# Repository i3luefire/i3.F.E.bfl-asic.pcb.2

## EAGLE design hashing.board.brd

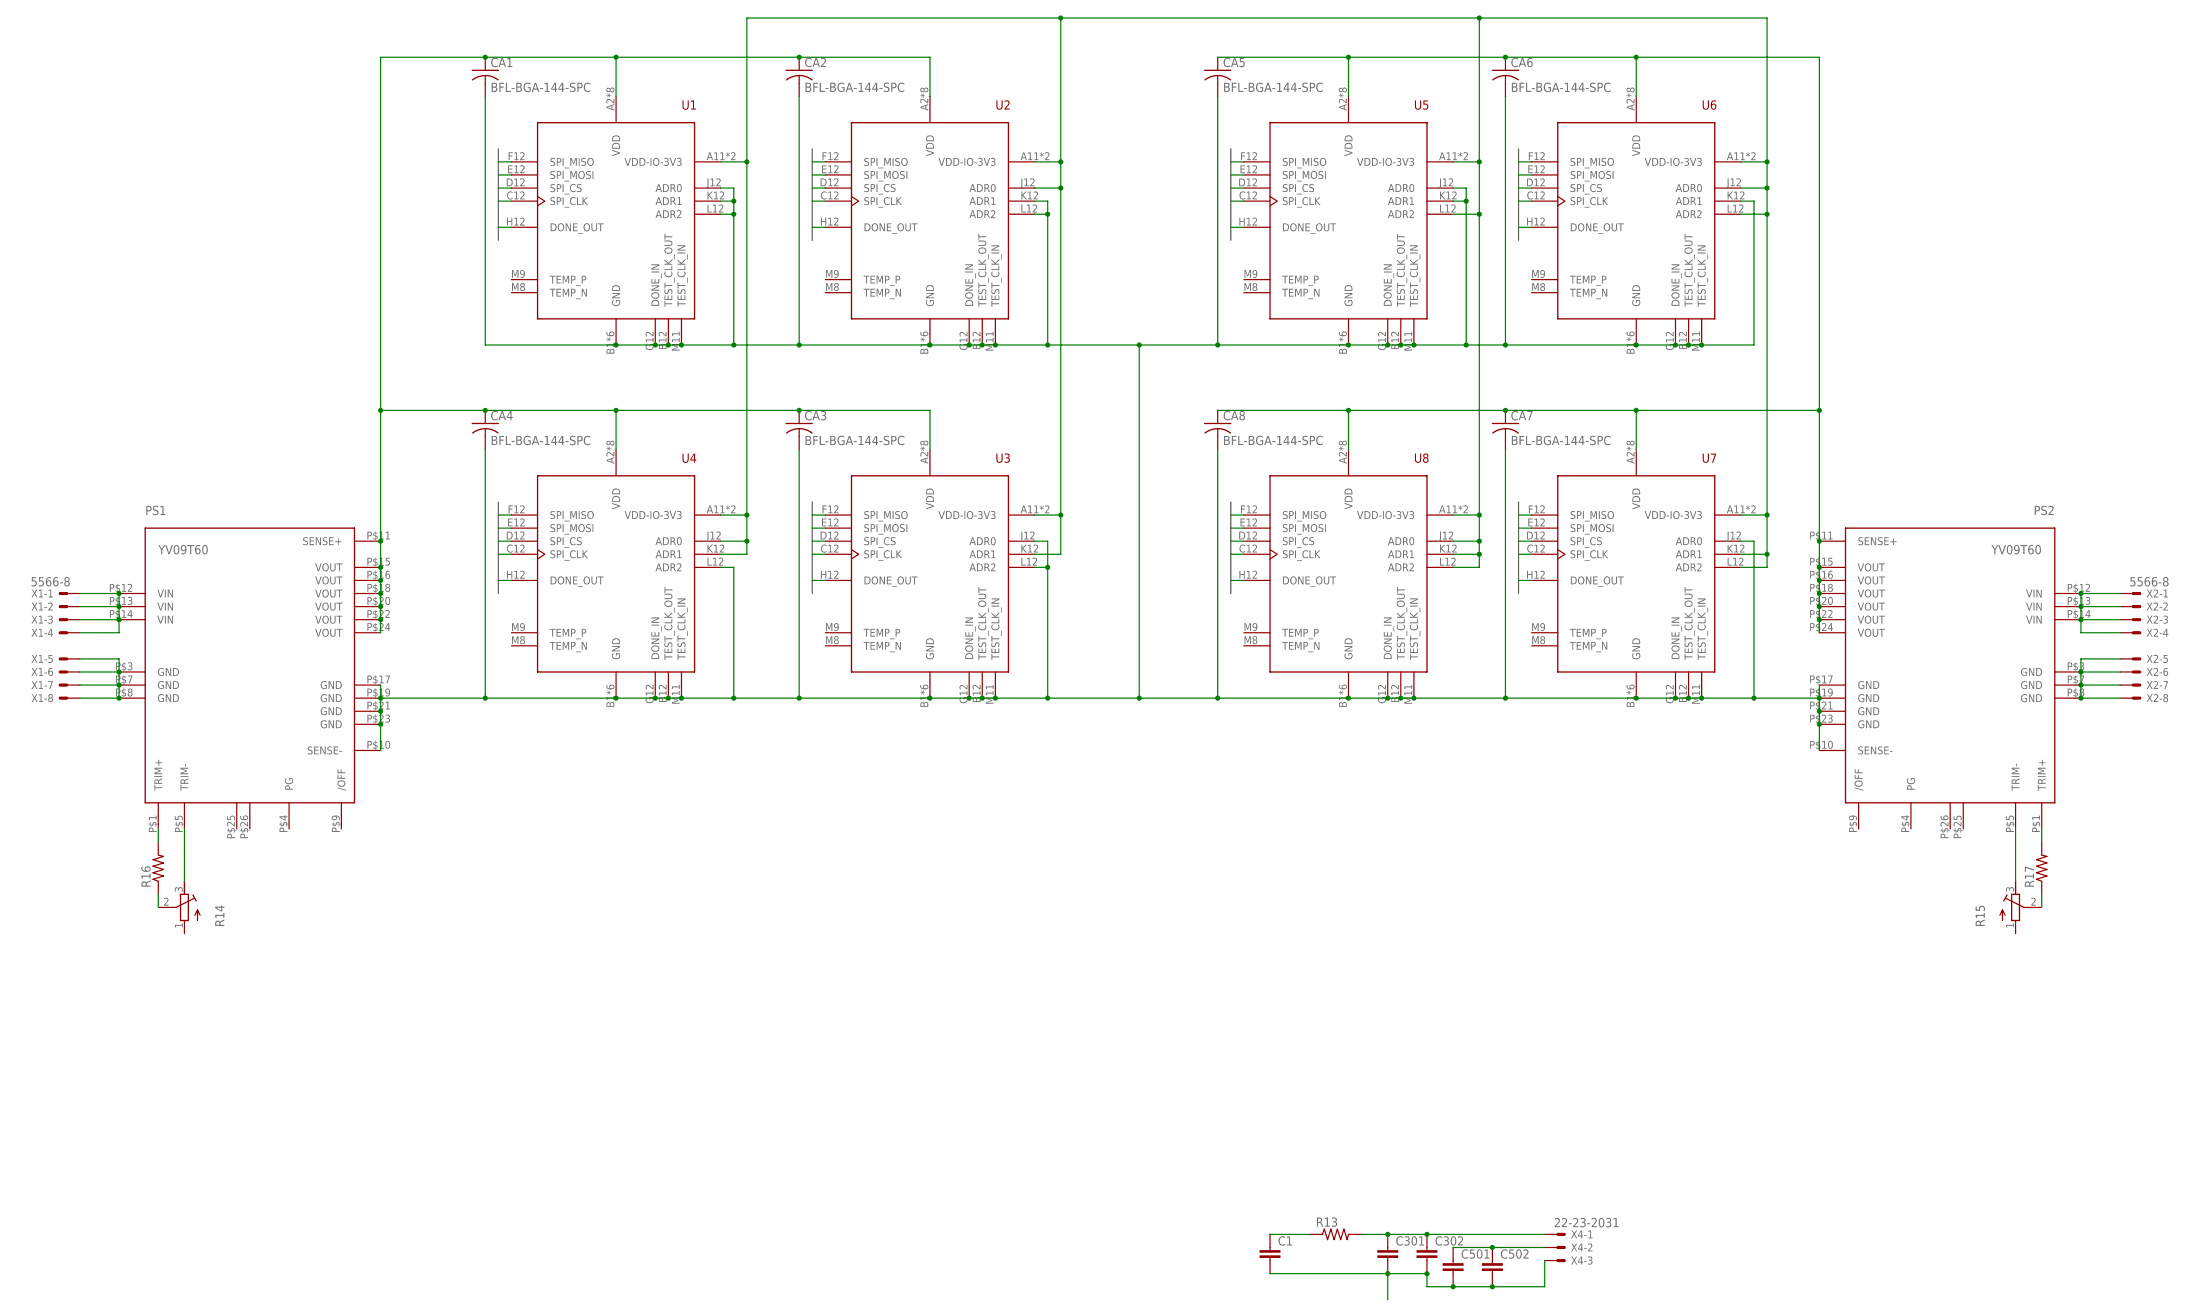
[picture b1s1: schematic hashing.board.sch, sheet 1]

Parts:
C1, C301, C501: C-EUC0805K; C0805K
C302, C502: C-EUC1210K; C1210K
CA1, CA2, CA3, CA4, CA5, CA6, CA7, CA8: BFL-BGA-144-SPC; BFL-BGA-VIA-PATTERN
PS1, PS2: YV09T60
R13, R16, R17: R-US_R0805W; R0805W
R14, R15: R-TRIMM3224J; RTRIM3224J
U1, U2, U3, U4, U5, U6, U7, U8: BFL-ASIC-1; BFL-BGA-BIG-PADS
X1, X2: 5566-8
X4: 22-23-2031

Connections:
DONE0: U1.H12 (DONE_OUT); also elsewhere on the board
DONE1: U2.H12 (DONE_OUT); also elsewhere on the board
DONE2: U3.H12 (DONE_OUT); also elsewhere on the board
DONE3: U4.H12 (DONE_OUT); also elsewhere on the board
DONE4: U5.H12 (DONE_OUT); also elsewhere on the board
DONE5: U6.H12 (DONE_OUT); also elsewhere on the board
DONE6: U8.H12 (DONE_OUT); also elsewhere on the board
DONE7: U7.H12 (DONE_OUT); also elsewhere on the board
GND: C1.2, C301.2, C302.2, C501.2, C502.2, CA1.N$2 (2), CA1.N$3 (2), CA1.N$5 (2), CA1.N$6 (2), CA1.N$8 (2), CA1.N$9 (2), CA1.N$11 (2), CA1.N$12 (2), CA1.N$14 (2), CA1.N$15 (2), CA1.N$16 (2), CA1.N$17 (2), CA1.N$19 (2), CA1.N$21 (2), CA1.N$23 (2), CA1.N$25 (2), CA1.N$27 (2), CA1.N$28 (2), CA1.N$30 (2), CA1.N$31 (2), CA1.N$33 (2), CA1.N$34 (2), CA1.N$36 (2), CA1.N$37 (2), CA1.N$39 (2), CA1.N$40 (2), CA1.N$42 (2), CA1.N$43 (2), CA1.N$44 (2), CA1.N$45 (2), CA1.N$55 (2), CA1.N$62 (2), CA1.N$64 (2), CA1.N$66 (2), CA1.N$68 (2), CA1.N$70 (2), CA1.N$72 (2), CA1.N$74 (2), CA1.N$76 (2), CA1.N$78 (2), CA1.N$80 (2), CA1.N$82 (2), CA1.N$84 (2), CA1.N$86 (2), CA1.N$88 (2), CA1.N$90 (2), CA1.N$92 (2), CA1.N$94 (2), CA1.N$98 (2), CA1.N$100 (2), CA1.N$102 (2), CA1.N$104 (2), CA1.N$106 (2), CA1.N$110 (2), CA2.N$2 (2), CA2.N$3 (2), CA2.N$5 (2), CA2.N$6 (2), CA2.N$8 (2), CA2.N$9 (2), CA2.N$11 (2), CA2.N$12 (2), CA2.N$14 (2), CA2.N$15 (2), CA2.N$16 (2), CA2.N$17 (2), CA2.N$19 (2), CA2.N$21 (2), CA2.N$23 (2), CA2.N$25 (2), CA2.N$27 (2), CA2.N$28 (2), CA2.N$30 (2), CA2.N$31 (2), CA2.N$33 (2), CA2.N$34 (2), CA2.N$36 (2), CA2.N$37 (2), CA2.N$39 (2), CA2.N$40 (2), CA2.N$42 (2), CA2.N$43 (2), CA2.N$44 (2), CA2.N$45 (2), CA2.N$55 (2), CA2.N$62 (2), CA2.N$64 (2), CA2.N$66 (2), CA2.N$68 (2), CA2.N$70 (2), CA2.N$72 (2), CA2.N$74 (2), CA2.N$76 (2), CA2.N$78 (2), CA2.N$80 (2), CA2.N$82 (2), CA2.N$84 (2), CA2.N$86 (2), CA2.N$88 (2), CA2.N$90 (2), CA2.N$92 (2), CA2.N$94 (2), CA2.N$98 (2), CA2.N$100 (2), CA2.N$102 (2), CA2.N$104 (2), CA2.N$106 (2), CA2.N$110 (2), CA3.N$2 (2), CA3.N$3 (2), CA3.N$5 (2), CA3.N$6 (2), CA3.N$8 (2), CA3.N$9 (2), CA3.N$11 (2), CA3.N$12 (2), CA3.N$14 (2), CA3.N$15 (2), CA3.N$16 (2), CA3.N$17 (2), CA3.N$19 (2), CA3.N$21 (2), CA3.N$23 (2), CA3.N$25 (2), CA3.N$27 (2), CA3.N$28 (2), CA3.N$30 (2), CA3.N$31 (2), CA3.N$33 (2), CA3.N$34 (2), CA3.N$36 (2), CA3.N$37 (2), CA3.N$39 (2), CA3.N$40 (2), CA3.N$42 (2), CA3.N$43 (2), CA3.N$44 (2), CA3.N$45 (2), CA3.N$55 (2), CA3.N$62 (2), CA3.N$64 (2), CA3.N$66 (2), CA3.N$68 (2), CA3.N$70 (2), CA3.N$72 (2), CA3.N$74 (2), CA3.N$76 (2), CA3.N$78 (2), CA3.N$80 (2), CA3.N$82 (2), CA3.N$84 (2), CA3.N$86 (2), CA3.N$88 (2), CA3.N$90 (2), CA3.N$92 (2), CA3.N$94 (2), CA3.N$98 (2), CA3.N$100 (2), CA3.N$102 (2), CA3.N$104 (2), CA3.N$106 (2), CA3.N$110 (2), CA4.N$2 (2), CA4.N$3 (2), CA4.N$5 (2), CA4.N$6 (2), CA4.N$8 (2), CA4.N$9 (2), CA4.N$11 (2), CA4.N$12 (2), CA4.N$14 (2), CA4.N$15 (2), CA4.N$16 (2), CA4.N$17 (2), CA4.N$19 (2), CA4.N$21 (2), CA4.N$23 (2), CA4.N$25 (2), CA4.N$27 (2), CA4.N$28 (2), CA4.N$30 (2), CA4.N$31 (2), CA4.N$33 (2), CA4.N$34 (2), CA4.N$36 (2), CA4.N$37 (2), CA4.N$39 (2), CA4.N$40 (2), CA4.N$42 (2), CA4.N$43 (2), CA4.N$44 (2), CA4.N$45 (2), CA4.N$55 (2), CA4.N$62 (2), CA4.N$64 (2), CA4.N$66 (2), CA4.N$68 (2), CA4.N$70 (2), CA4.N$72 (2), CA4.N$74 (2), CA4.N$76 (2), CA4.N$78 (2), CA4.N$80 (2), CA4.N$82 (2), CA4.N$84 (2), CA4.N$86 (2), CA4.N$88 (2), CA4.N$90 (2), CA4.N$92 (2), CA4.N$94 (2), CA4.N$98 (2), CA4.N$100 (2), CA4.N$102 (2), CA4.N$104 (2), CA4.N$106 (2), CA4.N$110 (2), CA5.N$2 (2), CA5.N$3 (2), CA5.N$5 (2), CA5.N$6 (2), CA5.N$8 (2), CA5.N$9 (2), CA5.N$11 (2), CA5.N$12 (2), CA5.N$14 (2), CA5.N$15 (2), CA5.N$16 (2), CA5.N$17 (2), CA5.N$19 (2), CA5.N$21 (2), CA5.N$23 (2), CA5.N$25 (2), CA5.N$27 (2), CA5.N$28 (2), CA5.N$30 (2), CA5.N$31 (2), CA5.N$33 (2), CA5.N$34 (2), CA5.N$36 (2), CA5.N$37 (2), CA5.N$39 (2), CA5.N$40 (2), CA5.N$42 (2), CA5.N$43 (2), CA5.N$44 (2), CA5.N$45 (2), CA5.N$55 (2), CA5.N$62 (2), CA5.N$64 (2), CA5.N$66 (2), CA5.N$68 (2), CA5.N$70 (2), CA5.N$72 (2), CA5.N$74 (2), CA5.N$76 (2), CA5.N$78 (2), CA5.N$80 (2), CA5.N$82 (2), CA5.N$84 (2), CA5.N$86 (2), CA5.N$88 (2), CA5.N$90 (2), CA5.N$92 (2), CA5.N$94 (2), CA5.N$98 (2), CA5.N$100 (2), CA5.N$102 (2), CA5.N$104 (2), CA5.N$106 (2), CA5.N$110 (2), CA6.N$2 (2), CA6.N$3 (2), CA6.N$5 (2), CA6.N$6 (2), CA6.N$8 (2), CA6.N$9 (2), CA6.N$11 (2), CA6.N$12 (2), CA6.N$14 (2), CA6.N$15 (2), CA6.N$16 (2), CA6.N$17 (2), CA6.N$19 (2), CA6.N$21 (2), CA6.N$23 (2), CA6.N$25 (2), CA6.N$27 (2), CA6.N$28 (2), CA6.N$30 (2), CA6.N$31 (2), CA6.N$33 (2), CA6.N$34 (2), CA6.N$36 (2), CA6.N$37 (2), CA6.N$39 (2), CA6.N$40 (2), CA6.N$42 (2), CA6.N$43 (2), CA6.N$44 (2), CA6.N$45 (2), CA6.N$55 (2), CA6.N$62 (2), CA6.N$64 (2), CA6.N$66 (2), CA6.N$68 (2), CA6.N$70 (2), CA6.N$72 (2), CA6.N$74 (2), CA6.N$76 (2), CA6.N$78 (2), CA6.N$80 (2), CA6.N$82 (2), CA6.N$84 (2), CA6.N$86 (2), CA6.N$88 (2), CA6.N$90 (2), CA6.N$92 (2), CA6.N$94 (2), CA6.N$98 (2), CA6.N$100 (2), CA6.N$102 (2), CA6.N$104 (2), CA6.N$106 (2), CA6.N$110 (2), CA7.N$2 (2), CA7.N$3 (2), CA7.N$5 (2), CA7.N$6 (2), CA7.N$8 (2), CA7.N$9 (2), CA7.N$11 (2), CA7.N$12 (2), CA7.N$14 (2), CA7.N$15 (2), CA7.N$16 (2), CA7.N$17 (2), CA7.N$19 (2), CA7.N$21 (2), CA7.N$23 (2), CA7.N$25 (2), CA7.N$27 (2), CA7.N$28 (2), CA7.N$30 (2), CA7.N$31 (2), CA7.N$33 (2), CA7.N$34 (2), CA7.N$36 (2), CA7.N$37 (2), CA7.N$39 (2), CA7.N$40 (2), CA7.N$42 (2), CA7.N$43 (2), CA7.N$44 (2), CA7.N$45 (2), CA7.N$55 (2), CA7.N$62 (2), CA7.N$64 (2), CA7.N$66 (2), CA7.N$68 (2), CA7.N$70 (2), CA7.N$72 (2), CA7.N$74 (2), CA7.N$76 (2), CA7.N$78 (2), CA7.N$80 (2), CA7.N$82 (2), CA7.N$84 (2), CA7.N$86 (2), CA7.N$88 (2), CA7.N$90 (2), CA7.N$92 (2), CA7.N$94 (2), CA7.N$98 (2), CA7.N$100 (2), CA7.N$102 (2), CA7.N$104 (2), CA7.N$106 (2), CA7.N$110 (2), CA8.N$2 (2), CA8.N$3 (2), CA8.N$5 (2), CA8.N$6 (2), CA8.N$8 (2), CA8.N$9 (2), CA8.N$11 (2), CA8.N$12 (2), CA8.N$14 (2), CA8.N$15 (2), CA8.N$16 (2), CA8.N$17 (2), CA8.N$19 (2), CA8.N$21 (2), CA8.N$23 (2), CA8.N$25 (2), CA8.N$27 (2), CA8.N$28 (2), CA8.N$30 (2), CA8.N$31 (2), CA8.N$33 (2), CA8.N$34 (2), CA8.N$36 (2), CA8.N$37 (2), CA8.N$39 (2), CA8.N$40 (2), CA8.N$42 (2), CA8.N$43 (2), CA8.N$44 (2), CA8.N$45 (2), CA8.N$55 (2), CA8.N$62 (2), CA8.N$64 (2), CA8.N$66 (2), CA8.N$68 (2), CA8.N$70 (2), CA8.N$72 (2), CA8.N$74 (2), CA8.N$76 (2), CA8.N$78 (2), CA8.N$80 (2), CA8.N$82 (2), CA8.N$84 (2), CA8.N$86 (2), CA8.N$88 (2), CA8.N$90 (2), CA8.N$92 (2), CA8.N$94 (2), CA8.N$98 (2), CA8.N$100 (2), CA8.N$102 (2), CA8.N$104 (2), CA8.N$106 (2), CA8.N$110 (2), PS1.P$3 (GND), PS1.P$7 (GND), PS1.P$8 (GND), PS1.P$10 (SENSE-), PS1.P$17 (GND), PS1.P$19 (GND), PS1.P$21 (GND), PS1.P$23 (GND), PS2.P$3 (GND), PS2.P$7 (GND), PS2.P$8 (GND), PS2.P$10 (SENSE-), PS2.P$17 (GND), PS2.P$19 (GND), PS2.P$21 (GND), PS2.P$23 (GND), U1.B1 (GND), U1.B3 (GND), U1.B5 (GND), U1.B7 (GND), U1.B9 (GND), U1.B11 (GND), U1.B12 (TEST_CLK_OUT), U1.G12 (DONE_IN), U1.J12 (ADR0), U1.K12 (ADR1), U1.L12 (ADR2), U1.M11 (TEST_CLK_IN), U2.B1 (GND), U2.B3 (GND), U2.B5 (GND), U2.B7 (GND), U2.B9 (GND), U2.B11 (GND), U2.B12 (TEST_CLK_OUT), U2.G12 (DONE_IN), U2.K12 (ADR1), U2.L12 (ADR2), U2.M11 (TEST_CLK_IN), U3.B1 (GND), U3.B3 (GND), U3.B5 (GND), U3.B7 (GND), U3.B9 (GND), U3.B11 (GND), U3.B12 (TEST_CLK_OUT), U3.G12 (DONE_IN), U3.J12 (ADR0), U3.L12 (ADR2), U3.M11 (TEST_CLK_IN), U4.B1 (GND), U4.B3 (GND), U4.B5 (GND), U4.B7 (GND), U4.B9 (GND), U4.B11 (GND), U4.B12 (TEST_CLK_OUT), U4.G12 (DONE_IN), U4.L12 (ADR2), U4.M11 (TEST_CLK_IN), U5.B1 (GND), U5.B3 (GND), U5.B5 (GND), U5.B7 (GND), U5.B9 (GND), U5.B11 (GND), U5.B12 (TEST_CLK_OUT), U5.G12 (DONE_IN), U5.J12 (ADR0), U5.K12 (ADR1), U5.M11 (TEST_CLK_IN), U6.B1 (GND), U6.B3 (GND), U6.B5 (GND), U6.B7 (GND), U6.B9 (GND), U6.B11 (GND), U6.B12 (TEST_CLK_OUT), U6.G12 (DONE_IN), U6.K12 (ADR1), U6.M11 (TEST_CLK_IN), U7.B1 (GND), U7.B3 (GND), U7.B5 (GND), U7.B7 (GND), U7.B9 (GND), U7.B11 (GND), U7.B12 (TEST_CLK_OUT), U7.G12 (DONE_IN), U7.J12 (ADR0), U7.M11 (TEST_CLK_IN), U8.B1 (GND), U8.B3 (GND), U8.B5 (GND), U8.B7 (GND), U8.B9 (GND), U8.B11 (GND), U8.B12 (TEST_CLK_OUT), U8.G12 (DONE_IN), U8.M11 (TEST_CLK_IN), X1.5, X1.6, X1.7, X1.8, X2.5, X2.6, X2.7, X2.8, X4.3; also elsewhere on the board
unnamed: R15.2 (S), R17.1
unnamed: PS2.P$1 (TRIM+), R17.2
unnamed: PS2.P$5 (TRIM-), R15.3 (A)
unnamed: PS1.P$5 (TRIM-), R14.3 (A)
unnamed: R14.2 (S), R16.1
unnamed: PS1.P$1 (TRIM+), R16.2
SPI_1_CLK: U1.C12 (SPI_CLK), U2.C12 (SPI_CLK), U3.C12 (SPI_CLK), U4.C12 (SPI_CLK), U5.C12 (SPI_CLK), U6.C12 (SPI_CLK), U7.C12 (SPI_CLK), U8.C12 (SPI_CLK); also elsewhere on the board
SPI_1_CS: U1.D12 (SPI_CS), U2.D12 (SPI_CS), U3.D12 (SPI_CS), U4.D12 (SPI_CS), U5.D12 (SPI_CS), U6.D12 (SPI_CS), U7.D12 (SPI_CS), U8.D12 (SPI_CS); also elsewhere on the board
SPI_1_MISO: U1.F12 (SPI_MISO), U2.F12 (SPI_MISO), U3.F12 (SPI_MISO), U4.F12 (SPI_MISO), U5.F12 (SPI_MISO), U6.F12 (SPI_MISO), U7.F12 (SPI_MISO), U8.F12 (SPI_MISO); also elsewhere on the board
SPI_1_MOSI: U1.E12 (SPI_MOSI), U2.E12 (SPI_MOSI), U3.E12 (SPI_MOSI), U4.E12 (SPI_MOSI), U5.E12 (SPI_MOSI), U6.E12 (SPI_MOSI), U7.E12 (SPI_MOSI), U8.E12 (SPI_MOSI); also elsewhere on the board
VDD-1A: CA1.P$1 (1), CA1.P$4 (1), CA1.P$7 (1), CA1.P$10 (1), CA1.P$13 (1), CA1.P$18 (1), CA1.P$20 (1), CA1.P$22 (1), CA1.P$24 (1), CA1.P$26 (1), CA1.P$29 (1), CA1.P$32 (1), CA1.P$35 (1), CA1.P$38 (1), CA1.P$41 (1), CA1.P$46 (1), CA1.P$47 (1), CA1.P$48 (1), CA1.P$50 (1), CA1.P$51 (1), CA1.P$52 (1), CA1.P$53 (1), CA1.P$54 (1), CA1.P$56 (1), CA1.P$57 (1), CA1.P$58 (1), CA1.P$59 (1), CA1.P$60 (1), CA1.P$61 (1), CA1.P$63 (1), CA1.P$65 (1), CA1.P$67 (1), CA1.P$69 (1), CA1.P$71 (1), CA1.P$73 (1), CA1.P$75 (1), CA1.P$77 (1), CA1.P$79 (1), CA1.P$81 (1), CA1.P$83 (1), CA1.P$85 (1), CA1.P$87 (1), CA1.P$89 (1), CA1.P$91 (1), CA1.P$93 (1), CA1.P$95 (1), CA1.P$99 (1), CA1.P$101 (1), CA1.P$103 (1), CA1.P$105 (1), CA1.P$107 (1), CA1.P$111 (1), CA2.P$1 (1), CA2.P$4 (1), CA2.P$7 (1), CA2.P$10 (1), CA2.P$13 (1), CA2.P$18 (1), CA2.P$20 (1), CA2.P$22 (1), CA2.P$24 (1), CA2.P$26 (1), CA2.P$29 (1), CA2.P$32 (1), CA2.P$35 (1), CA2.P$38 (1), CA2.P$41 (1), CA2.P$46 (1), CA2.P$47 (1), CA2.P$48 (1), CA2.P$50 (1), CA2.P$51 (1), CA2.P$52 (1), CA2.P$53 (1), CA2.P$54 (1), CA2.P$56 (1), CA2.P$57 (1), CA2.P$58 (1), CA2.P$59 (1), CA2.P$60 (1), CA2.P$61 (1), CA2.P$63 (1), CA2.P$65 (1), CA2.P$67 (1), CA2.P$69 (1), CA2.P$71 (1), CA2.P$73 (1), CA2.P$75 (1), CA2.P$77 (1), CA2.P$79 (1), CA2.P$81 (1), CA2.P$83 (1), CA2.P$85 (1), CA2.P$87 (1), CA2.P$89 (1), CA2.P$91 (1), CA2.P$93 (1), CA2.P$95 (1), CA2.P$99 (1), CA2.P$101 (1), CA2.P$103 (1), CA2.P$105 (1), CA2.P$107 (1), CA2.P$111 (1), CA3.P$1 (1), CA3.P$4 (1), CA3.P$7 (1), CA3.P$10 (1), CA3.P$13 (1), CA3.P$18 (1), CA3.P$20 (1), CA3.P$22 (1), CA3.P$24 (1), CA3.P$26 (1), CA3.P$29 (1), CA3.P$32 (1), CA3.P$35 (1), CA3.P$38 (1), CA3.P$41 (1), CA3.P$46 (1), CA3.P$47 (1), CA3.P$48 (1), CA3.P$50 (1), CA3.P$51 (1), CA3.P$52 (1), CA3.P$53 (1), CA3.P$54 (1), CA3.P$56 (1), CA3.P$57 (1), CA3.P$58 (1), CA3.P$59 (1), CA3.P$60 (1), CA3.P$61 (1), CA3.P$63 (1), CA3.P$65 (1), CA3.P$67 (1), CA3.P$69 (1), CA3.P$71 (1), CA3.P$73 (1), CA3.P$75 (1), CA3.P$77 (1), CA3.P$79 (1), CA3.P$81 (1), CA3.P$83 (1), CA3.P$85 (1), CA3.P$87 (1), CA3.P$89 (1), CA3.P$91 (1), CA3.P$93 (1), CA3.P$95 (1), CA3.P$99 (1), CA3.P$101 (1), CA3.P$103 (1), CA3.P$105 (1), CA3.P$107 (1), CA3.P$111 (1), CA4.P$1 (1), CA4.P$4 (1), CA4.P$7 (1), CA4.P$10 (1), CA4.P$13 (1), CA4.P$18 (1), CA4.P$20 (1), CA4.P$22 (1), CA4.P$24 (1), CA4.P$26 (1), CA4.P$29 (1), CA4.P$32 (1), CA4.P$35 (1), CA4.P$38 (1), CA4.P$41 (1), CA4.P$46 (1), CA4.P$47 (1), CA4.P$48 (1), CA4.P$50 (1), CA4.P$51 (1), CA4.P$52 (1), CA4.P$53 (1), CA4.P$54 (1), CA4.P$56 (1), CA4.P$57 (1), CA4.P$58 (1), CA4.P$59 (1), CA4.P$60 (1), CA4.P$61 (1), CA4.P$63 (1), CA4.P$65 (1), CA4.P$67 (1), CA4.P$69 (1), CA4.P$71 (1), CA4.P$73 (1), CA4.P$75 (1), CA4.P$77 (1), CA4.P$79 (1), CA4.P$81 (1), CA4.P$83 (1), CA4.P$85 (1), CA4.P$87 (1), CA4.P$89 (1), CA4.P$91 (1), CA4.P$93 (1), CA4.P$95 (1), CA4.P$99 (1), CA4.P$101 (1), CA4.P$103 (1), CA4.P$105 (1), CA4.P$107 (1), CA4.P$111 (1), PS1.P$11 (SENSE+), PS1.P$15 (VOUT), PS1.P$16 (VOUT), PS1.P$18 (VOUT), PS1.P$20 (VOUT), PS1.P$22 (VOUT), PS1.P$24 (VOUT), U1.A2 (VDD), U1.A4 (VDD), U1.A6 (VDD), U1.A8 (VDD), U1.A9 (VDD), U1.A10 (VDD), U1.M5 (VDD), U1.M7 (VDD), U2.A2 (VDD), U2.A4 (VDD), U2.A6 (VDD), U2.A8 (VDD), U2.A9 (VDD), U2.A10 (VDD), U2.M5 (VDD), U2.M7 (VDD), U3.A2 (VDD), U3.A4 (VDD), U3.A6 (VDD), U3.A8 (VDD), U3.A9 (VDD), U3.A10 (VDD), U3.M5 (VDD), U3.M7 (VDD), U4.A2 (VDD), U4.A4 (VDD), U4.A6 (VDD), U4.A8 (VDD), U4.A9 (VDD), U4.A10 (VDD), U4.M5 (VDD), U4.M7 (VDD)
VDD-1B: CA5.P$1 (1), CA5.P$4 (1), CA5.P$7 (1), CA5.P$10 (1), CA5.P$13 (1), CA5.P$18 (1), CA5.P$20 (1), CA5.P$22 (1), CA5.P$24 (1), CA5.P$26 (1), CA5.P$29 (1), CA5.P$32 (1), CA5.P$35 (1), CA5.P$38 (1), CA5.P$41 (1), CA5.P$46 (1), CA5.P$47 (1), CA5.P$48 (1), CA5.P$50 (1), CA5.P$51 (1), CA5.P$52 (1), CA5.P$53 (1), CA5.P$54 (1), CA5.P$56 (1), CA5.P$57 (1), CA5.P$58 (1), CA5.P$59 (1), CA5.P$60 (1), CA5.P$61 (1), CA5.P$63 (1), CA5.P$65 (1), CA5.P$67 (1), CA5.P$69 (1), CA5.P$71 (1), CA5.P$73 (1), CA5.P$75 (1), CA5.P$77 (1), CA5.P$79 (1), CA5.P$81 (1), CA5.P$83 (1), CA5.P$85 (1), CA5.P$87 (1), CA5.P$89 (1), CA5.P$91 (1), CA5.P$93 (1), CA5.P$95 (1), CA5.P$99 (1), CA5.P$101 (1), CA5.P$103 (1), CA5.P$105 (1), CA5.P$107 (1), CA5.P$111 (1), CA6.P$1 (1), CA6.P$4 (1), CA6.P$7 (1), CA6.P$10 (1), CA6.P$13 (1), CA6.P$18 (1), CA6.P$20 (1), CA6.P$22 (1), CA6.P$24 (1), CA6.P$26 (1), CA6.P$29 (1), CA6.P$32 (1), CA6.P$35 (1), CA6.P$38 (1), CA6.P$41 (1), CA6.P$46 (1), CA6.P$47 (1), CA6.P$48 (1), CA6.P$50 (1), CA6.P$51 (1), CA6.P$52 (1), CA6.P$53 (1), CA6.P$54 (1), CA6.P$56 (1), CA6.P$57 (1), CA6.P$58 (1), CA6.P$59 (1), CA6.P$60 (1), CA6.P$61 (1), CA6.P$63 (1), CA6.P$65 (1), CA6.P$67 (1), CA6.P$69 (1), CA6.P$71 (1), CA6.P$73 (1), CA6.P$75 (1), CA6.P$77 (1), CA6.P$79 (1), CA6.P$81 (1), CA6.P$83 (1), CA6.P$85 (1), CA6.P$87 (1), CA6.P$89 (1), CA6.P$91 (1), CA6.P$93 (1), CA6.P$95 (1), CA6.P$99 (1), CA6.P$101 (1), CA6.P$103 (1), CA6.P$105 (1), CA6.P$107 (1), CA6.P$111 (1), CA7.P$1 (1), CA7.P$4 (1), CA7.P$7 (1), CA7.P$10 (1), CA7.P$13 (1), CA7.P$18 (1), CA7.P$20 (1), CA7.P$22 (1), CA7.P$24 (1), CA7.P$26 (1), CA7.P$29 (1), CA7.P$32 (1), CA7.P$35 (1), CA7.P$38 (1), CA7.P$41 (1), CA7.P$46 (1), CA7.P$47 (1), CA7.P$48 (1), CA7.P$50 (1), CA7.P$51 (1), CA7.P$52 (1), CA7.P$53 (1), CA7.P$54 (1), CA7.P$56 (1), CA7.P$57 (1), CA7.P$58 (1), CA7.P$59 (1), CA7.P$60 (1), CA7.P$61 (1), CA7.P$63 (1), CA7.P$65 (1), CA7.P$67 (1), CA7.P$69 (1), CA7.P$71 (1), CA7.P$73 (1), CA7.P$75 (1), CA7.P$77 (1), CA7.P$79 (1), CA7.P$81 (1), CA7.P$83 (1), CA7.P$85 (1), CA7.P$87 (1), CA7.P$89 (1), CA7.P$91 (1), CA7.P$93 (1), CA7.P$95 (1), CA7.P$99 (1), CA7.P$101 (1), CA7.P$103 (1), CA7.P$105 (1), CA7.P$107 (1), CA7.P$111 (1), CA8.P$1 (1), CA8.P$4 (1), CA8.P$7 (1), CA8.P$10 (1), CA8.P$13 (1), CA8.P$18 (1), CA8.P$20 (1), CA8.P$22 (1), CA8.P$24 (1), CA8.P$26 (1), CA8.P$29 (1), CA8.P$32 (1), CA8.P$35 (1), CA8.P$38 (1), CA8.P$41 (1), CA8.P$46 (1), CA8.P$47 (1), CA8.P$48 (1), CA8.P$50 (1), CA8.P$51 (1), CA8.P$52 (1), CA8.P$53 (1), CA8.P$54 (1), CA8.P$56 (1), CA8.P$57 (1), CA8.P$58 (1), CA8.P$59 (1), CA8.P$60 (1), CA8.P$61 (1), CA8.P$63 (1), CA8.P$65 (1), CA8.P$67 (1), CA8.P$69 (1), CA8.P$71 (1), CA8.P$73 (1), CA8.P$75 (1), CA8.P$77 (1), CA8.P$79 (1), CA8.P$81 (1), CA8.P$83 (1), CA8.P$85 (1), CA8.P$87 (1), CA8.P$89 (1), CA8.P$91 (1), CA8.P$93 (1), CA8.P$95 (1), CA8.P$99 (1), CA8.P$101 (1), CA8.P$103 (1), CA8.P$105 (1), CA8.P$107 (1), CA8.P$111 (1), PS2.P$11 (SENSE+), PS2.P$15 (VOUT), PS2.P$16 (VOUT), PS2.P$18 (VOUT), PS2.P$20 (VOUT), PS2.P$22 (VOUT), PS2.P$24 (VOUT), U5.A2 (VDD), U5.A4 (VDD), U5.A6 (VDD), U5.A8 (VDD), U5.A9 (VDD), U5.A10 (VDD), U5.M5 (VDD), U5.M7 (VDD), U6.A2 (VDD), U6.A4 (VDD), U6.A6 (VDD), U6.A8 (VDD), U6.A9 (VDD), U6.A10 (VDD), U6.M5 (VDD), U6.M7 (VDD), U7.A2 (VDD), U7.A4 (VDD), U7.A6 (VDD), U7.A8 (VDD), U7.A9 (VDD), U7.A10 (VDD), U7.M5 (VDD), U7.M7 (VDD), U8.A2 (VDD), U8.A4 (VDD), U8.A6 (VDD), U8.A8 (VDD), U8.A9 (VDD), U8.A10 (VDD), U8.M5 (VDD), U8.M7 (VDD)
VDD-3V3: C1.1, R13.1, U1.A11 (VDD-IO-3V3), U1.M10 (VDD-IO-3V3), U2.A11 (VDD-IO-3V3), U2.J12 (ADR0), U2.M10 (VDD-IO-3V3), U3.A11 (VDD-IO-3V3), U3.K12 (ADR1), U3.M10 (VDD-IO-3V3), U4.A11 (VDD-IO-3V3), U4.J12 (ADR0), U4.K12 (ADR1), U4.M10 (VDD-IO-3V3), U5.A11 (VDD-IO-3V3), U5.L12 (ADR2), U5.M10 (VDD-IO-3V3), U6.A11 (VDD-IO-3V3), U6.J12 (ADR0), U6.L12 (ADR2), U6.M10 (VDD-IO-3V3), U7.A11 (VDD-IO-3V3), U7.K12 (ADR1), U7.L12 (ADR2), U7.M10 (VDD-IO-3V3), U8.A11 (VDD-IO-3V3), U8.J12 (ADR0), U8.K12 (ADR1), U8.L12 (ADR2), U8.M10 (VDD-IO-3V3)
VIN1: PS1.P$12 (VIN), PS1.P$13 (VIN), PS1.P$14 (VIN), X1.1, X1.2, X1.3, X1.4
VIN2: PS2.P$12 (VIN), PS2.P$13 (VIN), PS2.P$14 (VIN), X2.1, X2.2, X2.3, X2.4
VIN-3.3V: C301.1, C302.1, R13.2, X4.1
VIN-5.0V: C501.1, C502.1, X4.2

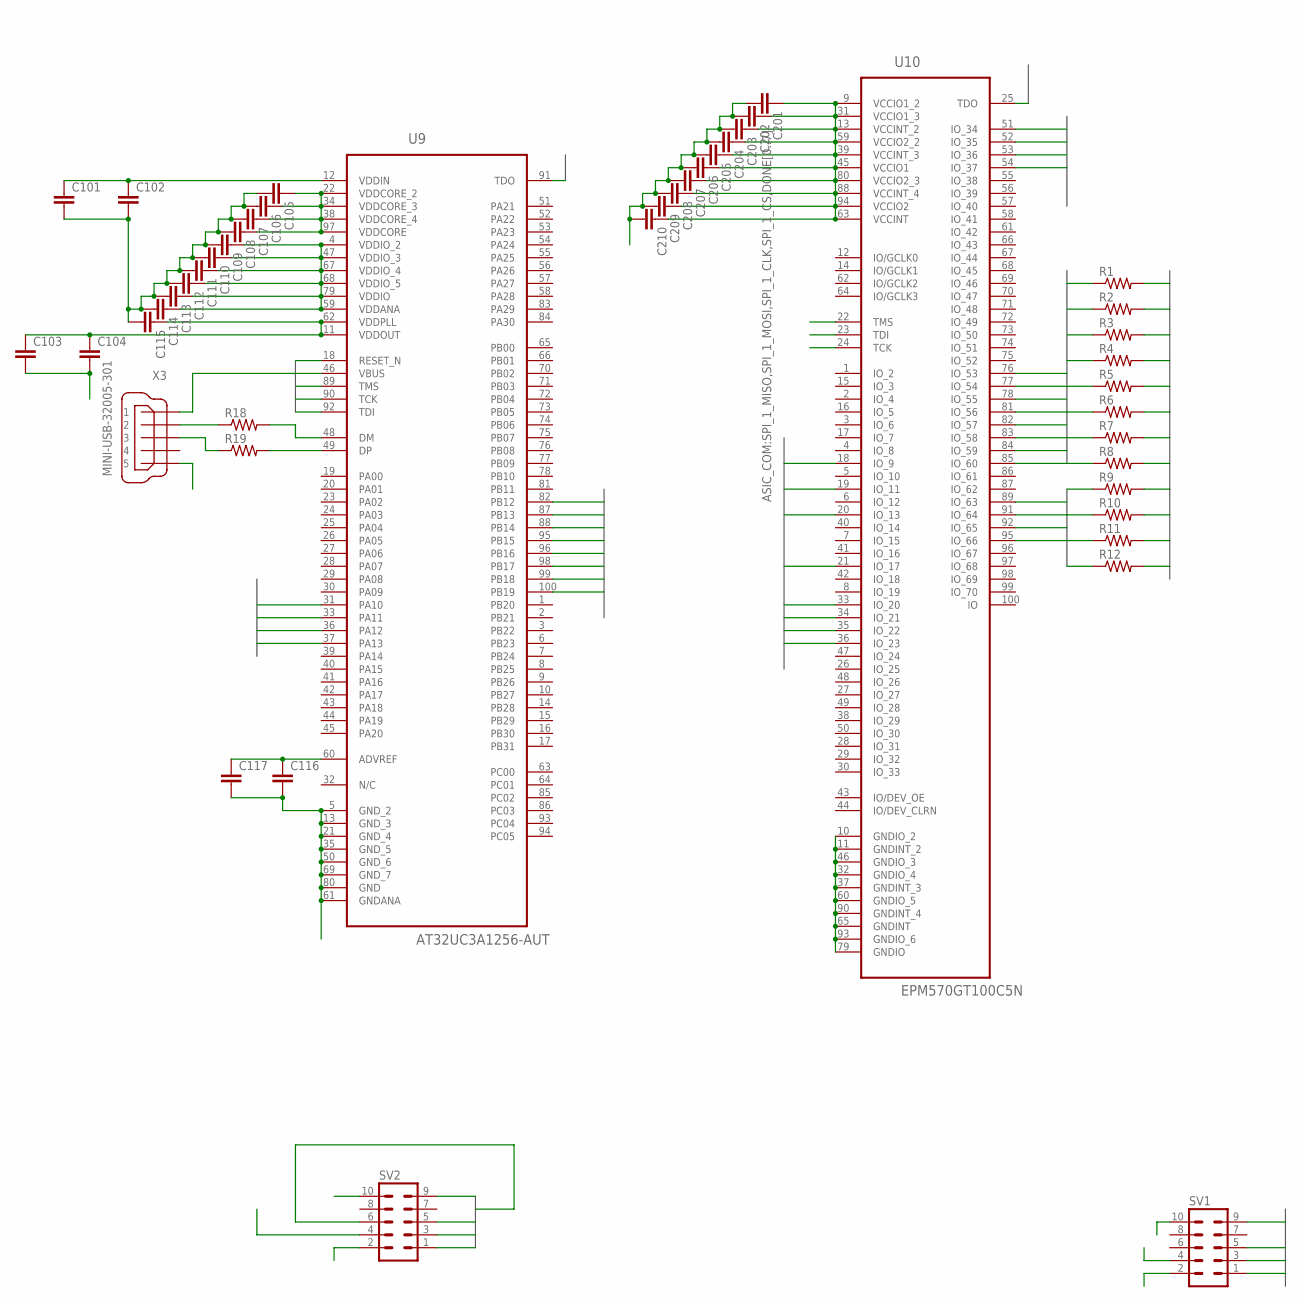
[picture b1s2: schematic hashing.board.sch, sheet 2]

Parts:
C101, C102, C103, C104, C105, C106, C107, C108, C109, C110, C111, C112, C113, C114, C115, C116, C117, C201, C202, C203, C204, C205, C206, C207, C208, C209, C210: C-EUC0402; C0402
R1, R2, R3, R4, R5, R6, R7, R8, R9, R10, R11, R12: R-US_R0201; R0201
R18, R19: R-US_R0603; R0603
SV1, SV2: MA05-2
U9: AT32UC3A1256-AUT; QFP50P1600X1600X120-100N
U10: EPM570GT100C5N; QFP50P1600X1600X120-100N
X3: MINI-USB-32005-301; 32005-301

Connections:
ATMEL_RST: SV2.6, U9.18 (RESET_N)
ATMEL_TCK: SV2.1, U9.90 (TCK)
ATMEL_TDI: SV2.9, U9.92 (TDI)
ATMEL_TDO: SV2.3, U9.91 (TDO)
ATMEL_TMS: SV2.5, U9.89 (TMS)
CHECK_VOLTAGE: U9.46 (VBUS), X3.1
CPLD_TCK: SV1.1, U10.24 (TCK)
CPLD_TDI: SV1.9, U10.23 (TDI)
CPLD_TDO: SV1.3, U10.25 (TDO)
CPLD_TMS: SV1.5, U10.22 (TMS)
DONE0: R1.2, U10.18 (IO_9); also elsewhere on the board
DONE1: R2.2, U10.19 (IO_11); also elsewhere on the board
DONE2: R3.2, U10.20 (IO_13); also elsewhere on the board
DONE3: R4.2, U10.21 (IO_17); also elsewhere on the board
DONE4: R5.2, U10.51 (IO_34); also elsewhere on the board
DONE5: R6.2, U10.52 (IO_35); also elsewhere on the board
DONE6: R7.2, U10.53 (IO_36); also elsewhere on the board
DONE7: R8.2, U10.54 (IO_37); also elsewhere on the board
DONE_0: R1.1, U9.82 (PB12), U10.76 (IO_53)
DONE_1: R2.1, U9.87 (PB13), U10.77 (IO_54)
DONE_2: R3.1, U9.88 (PB14), U10.78 (IO_55)
DONE_3: R4.1, U9.95 (PB15), U10.81 (IO_56)
DONE_4: R5.1, U9.96 (PB16), U10.82 (IO_57)
DONE_5: R6.1, U9.98 (PB17), U10.83 (IO_58)
DONE_6: R7.1, U9.99 (PB18), U10.84 (IO_59)
DONE_7: R8.1, U9.100 (PB19), U10.85 (IO_60)
GND: C101.2, C102.2, C103.2, C104.2, C105.2, C106.2, C107.2, C108.2, C109.2, C110.2, C111.2, C112.2, C113.2, C114.2, C115.2, C116.2, C117.2, C201.2, C202.2, C203.2, C204.2, C205.2, C206.2, C207.2, C208.2, C209.2, C210.2, SV1.2, SV1.10, SV2.2, SV2.10, U9.5 (GND_2), U9.13 (GND_3), U9.21 (GND_4), U9.35 (GND_5), U9.50 (GND_6), U9.61 (GNDANA), U9.69 (GND_7), U9.80 (GND), U10.10 (GNDIO_2), U10.11 (GNDINT_2), U10.32 (GNDIO_4), U10.37 (GNDINT_3), U10.46 (GNDIO_3), U10.60 (GNDIO_5), U10.65 (GNDINT), U10.79 (GNDIO), U10.90 (GNDINT_4), U10.93 (GNDIO_6), X3.5; also elsewhere on the board
unnamed: R18.1, X3.2
unnamed: R19.1, X3.3
unnamed: R19.2, U9.49 (DP)
unnamed: R18.2, U9.48 (DM)
SPI_1_CLK: R11.2, U10.35 (IO_22); also elsewhere on the board
SPI_1_CLK_: R11.1, U9.37 (PA13), U10.89 (IO_63)
SPI_1_CS: R12.2, U10.36 (IO_23); also elsewhere on the board
SPI_1_CS_: R12.1, U9.31 (PA10), U10.95 (IO_66)
SPI_1_MISO: R9.2, U10.33 (IO_20); also elsewhere on the board
SPI_1_MISO_: R9.1, U9.33 (PA11), U10.92 (IO_65)
SPI_1_MOSI: R10.2, U10.34 (IO_21); also elsewhere on the board
SPI_1_MOSI_: R10.1, U9.36 (PA12), U10.91 (IO_64)
VCC+1V8: C103.1, C104.1, C105.1, C106.1, C107.1, C108.1, C115.1, U9.11 (VDDOUT), U9.22 (VDDCORE_2), U9.34 (VDDCORE_3), U9.38 (VDDCORE_4), U9.62 (VDDPLL), U9.97 (VDDCORE)
VCC+3V3: C101.1, C102.1, C109.1, C110.1, C111.1, C112.1, C113.1, C114.1, C116.1, C117.1, C201.1, C202.1, C203.1, C204.1, C205.1, C206.1, C207.1, C208.1, C209.1, C210.1, SV1.4, SV2.4, U9.4 (VDDIO_2), U9.12 (VDDIN), U9.47 (VDDIO_3), U9.59 (VDDANA), U9.60 (ADVREF), U9.67 (VDDIO_4), U9.68 (VDDIO_5), U9.79 (VDDIO), U10.9 (VCCIO1_2), U10.13 (VCCINT_2), U10.31 (VCCIO1_3), U10.39 (VCCINT_3), U10.45 (VCCIO1), U10.59 (VCCIO2_2), U10.63 (VCCINT), U10.80 (VCCIO2_3), U10.88 (VCCINT_4), U10.94 (VCCIO2)

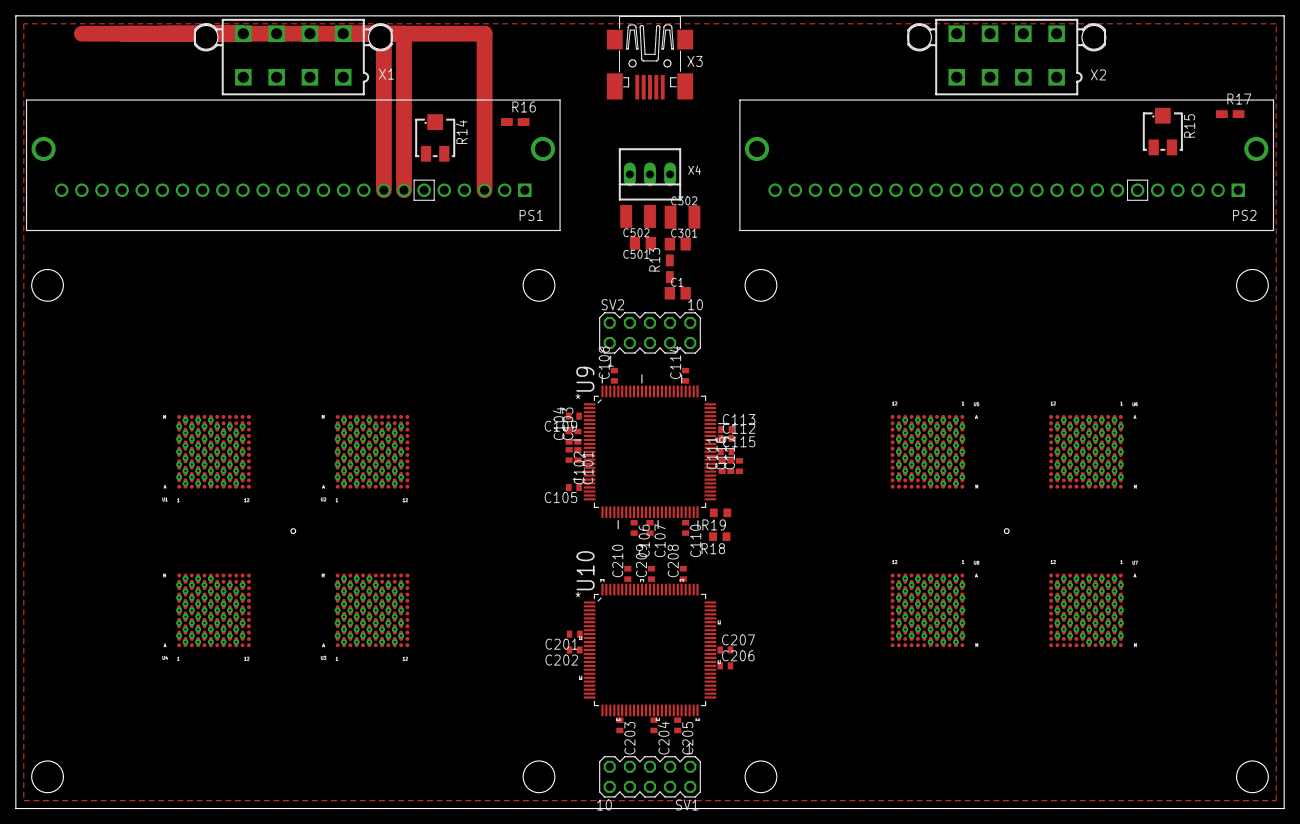
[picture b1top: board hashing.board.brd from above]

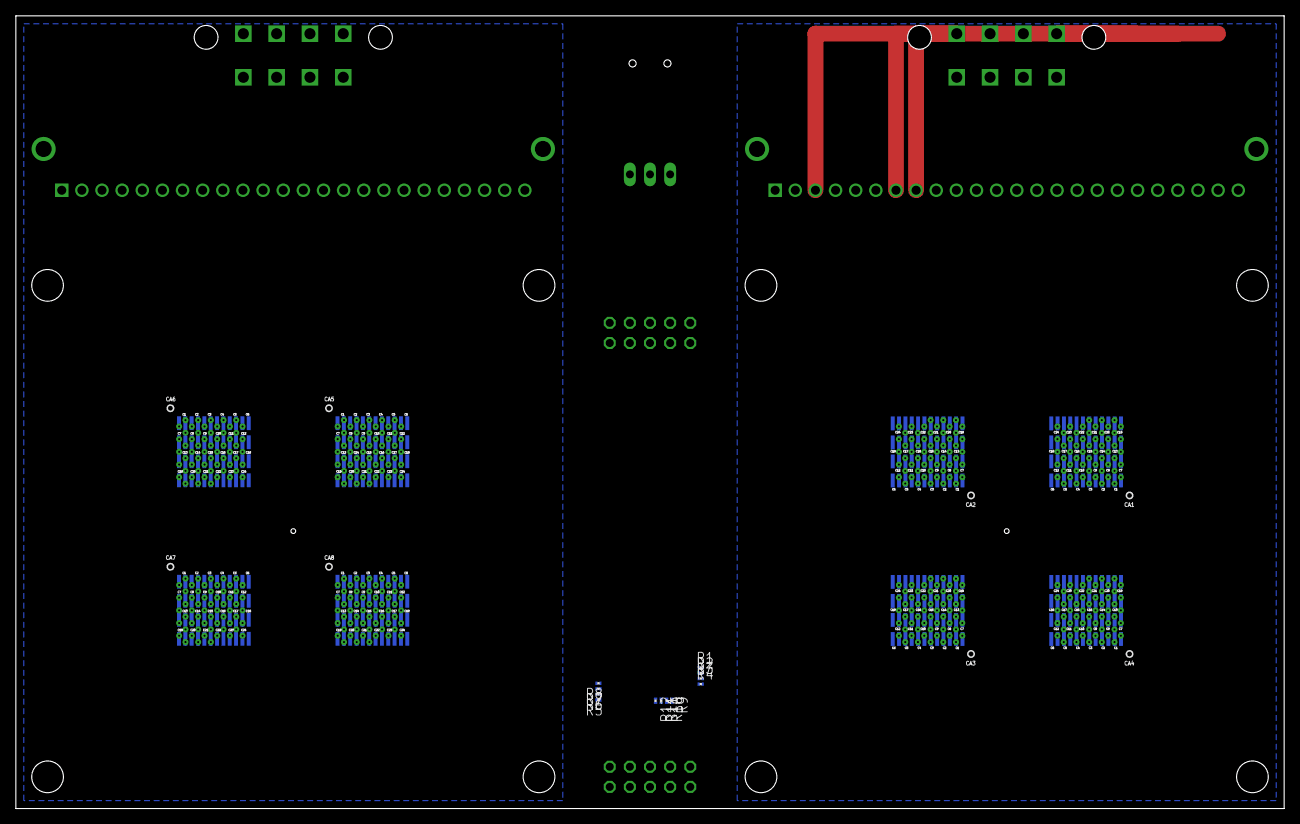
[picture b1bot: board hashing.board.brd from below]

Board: 4 copper layers, 160.0 x 100.0 mm, 77 parts (20 on the bottom side), 54 nets.

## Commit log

2013-09-14 changed gitignore for eagle cad
